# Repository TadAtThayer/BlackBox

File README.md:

# Black Box

ES22 black box carrier board.  

Converted to KiCad from Jason Stauth's original Eagle version.

Mostly because I don't love Eagle.

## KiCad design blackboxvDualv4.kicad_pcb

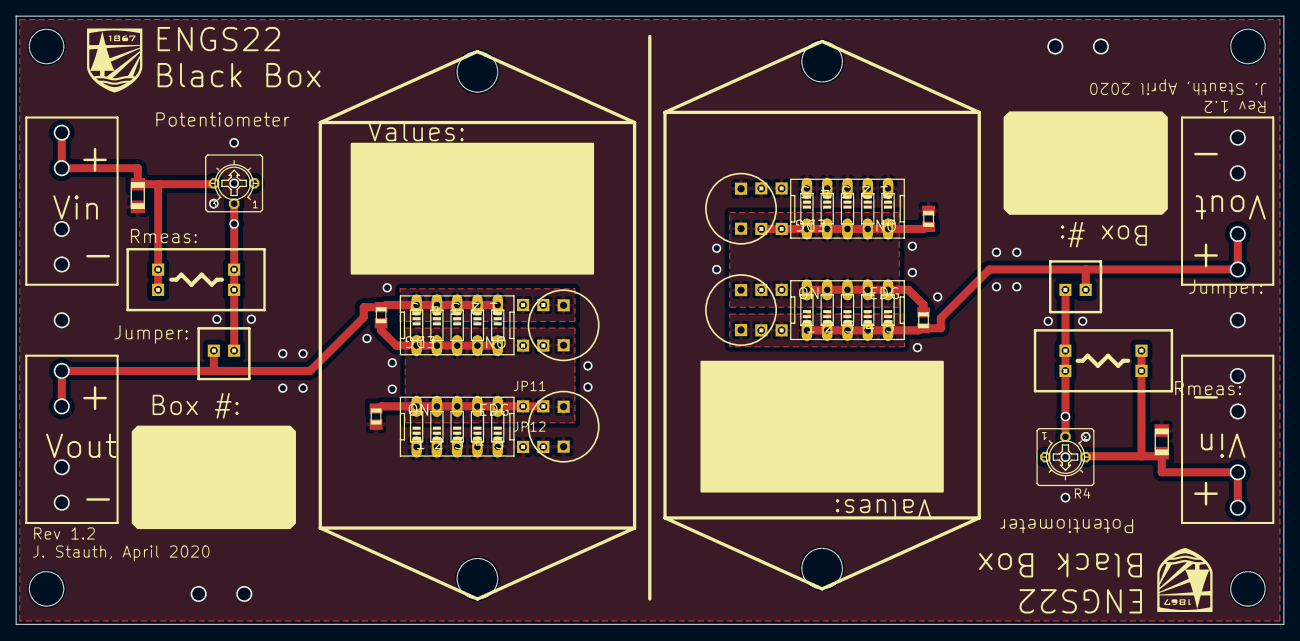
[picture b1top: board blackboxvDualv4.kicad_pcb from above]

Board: 2 copper layers, 158.8 x 76.2 mm, 40 parts (0 on the bottom side), 9 nets.

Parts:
C1, C2, C3, C4: C0805K
JP1, JP2, JP3, JP4, JP5, JP6, JP7, JP8, JP9, JP10, JP11, JP12, JP13, JP14: 1X02
L1, L2, L3, L4: 6000-XXXX-RC
R1, R2: R1206
R3, R4: CT6
SW1, SW2, SW3, SW4: EDG-05
U$1, U$2: Val**; THAYER
UNK_HOLE_0: dummyfp0
UNK_HOLE_1: dummyfp1
UNK_HOLE_2: dummyfp2
UNK_HOLE_3: dummyfp3
UNK_HOLE_4: dummyfp4
UNK_HOLE_5: dummyfp5
UNK_HOLE_6: dummyfp6
UNK_HOLE_7: dummyfp7

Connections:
GND: C2.2, C4.2, JP12.1, JP12.2, JP14.1, JP14.2, L1.2, L3.2, R1.1, R2.1, SW2.1, SW2.2, SW2.3, SW2.4, SW2.5, SW4.1, SW4.2, SW4.3, SW4.4, SW4.5
unnamed: JP3.1, JP4.1, JP4.2, R3.S
unnamed: C1.2, C2.1, JP8.1, JP8.2, JP11.1, JP11.2, L1.1, L2.2, SW1.6, SW1.7, SW1.8, SW1.9, SW1.10, SW2.6, SW2.7, SW2.8, SW2.9, SW2.10
VIN: JP2.1, JP2.2, R1.2, R3.E
VIN2: JP5.1, JP5.2, R2.2, R4.E
VOUT: C1.1, JP3.2, JP7.1, JP7.2, L2.1, SW1.1, SW1.2, SW1.3, SW1.4, SW1.5
VOUT2: C3.1, JP1.2, JP10.1, JP10.2, L4.1, SW3.1, SW3.2, SW3.3, SW3.4, SW3.5
VP2: JP1.1, JP6.1, JP6.2, R4.S
VX2: C3.2, C4.1, JP9.1, JP9.2, JP13.1, JP13.2, L3.1, L4.2, SW3.6, SW3.7, SW3.8, SW3.9, SW3.10, SW4.6, SW4.7, SW4.8, SW4.9, SW4.10

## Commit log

2025-07-30 initial import of V1.2
2025-07-30 generate gerbers
2025-07-30 Rename gerbers to make them easier to find in the vast wasteland of my PCB ordering history.
